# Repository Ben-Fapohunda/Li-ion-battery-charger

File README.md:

# USB-C Smart Li-ion Charger with Live Battery Monitor

A compact single-cell Li-ion/LiPo charger powered over USB-C, with a built-in monitor that shows battery voltage and charge current on a small OLED. The project is designed end to end in KiCad, covering component selection, schematic capture, and PCB layout, and serves as a reference design for small portable power systems.

## Overview

Most low-cost chargers charge a battery and reveal nothing about what is happening. This design adds visibility: voltage and current are measured and displayed in real time while charging, and the power-path architecture lets the board supply a load at the same time.

## Features

- USB-C power input
- Single-cell Li-ion/LiPo charging using the MCP73871 charge management IC, with power-path control
- Voltage and current sensing using an INA219 and a shunt resistor over I2C
- ATtiny1614 microcontroller that reads the sensor and drives a 0.91" I2C OLED
- CH340C USB-to-UART bridge for programming and serial debugging
- AMS1117-3.3 regulator for the logic supply

## Design Approach

The board is split into three functional blocks: power and charging, measurement, and control and display.

Component values were selected around the following:

- **Charge current:** 1 A, set by R_PROG1 = 1 kΩ on the MCP73871 (I = 1000 / R_PROG1 in kΩ)
- **Current sensing:** shunt resistance matched to the INA219 input range
- **Logic supply:** 3.3 V rail from the AMS1117-3.3

The layout is a compact 2-layer board, with attention to current-carrying traces and the placement of the sense resistor.

## Tools

- KiCad for schematic and PCB design
- Arduino/megaTinyCore for ATtiny1614 firmware

## Repository Contents

- `battery charger/`: KiCad project files (schematic and PCB)
- `pcb.png`: PCB layout screenshot
- `pcb view.png`: PCB view screenshot
- `README.md`: project description

## Status

Schematic and PCB layout complete. Not yet fabricated or tested. Photos and measured results will be added after the board is built and tested.

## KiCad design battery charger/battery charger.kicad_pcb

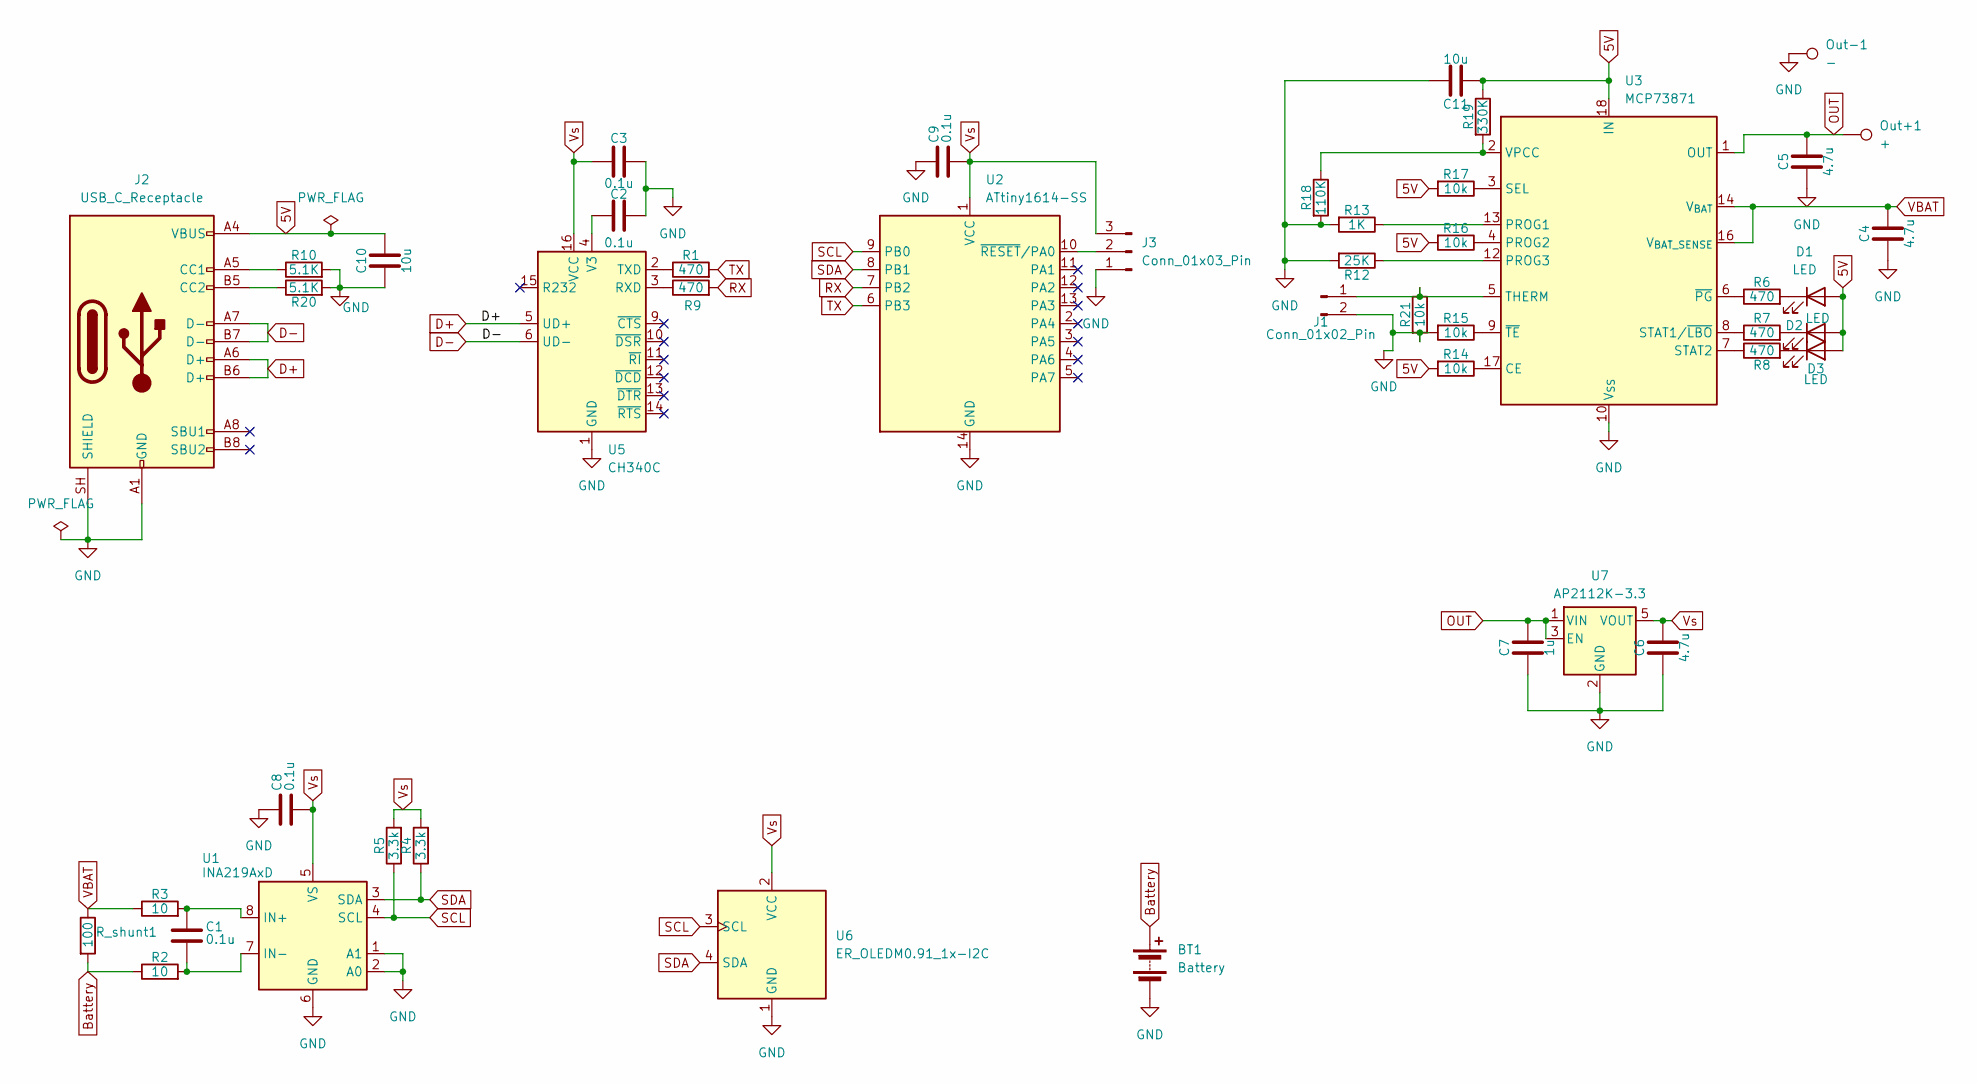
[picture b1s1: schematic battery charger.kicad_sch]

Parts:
BT1: Battery; BatteryHolder_Keystone_2460_1xAA
C1, C2, C3, C8, C9: 0.1u; C_0805_2012Metric
C4, C5, C6: 4.7u; C_0805_2012Metric
C7: 1u; C_0805_2012Metric
C10, C11: 10u; C_0805_2012Metric
D1, D2, D3: LED; LED_0805_2012Metric
J1: Conn_01x02_Pin; PinSocket_1x02_P1.27mm_Vertical
J2: USB_C_Receptacle; USB_C_Receptacle_HRO_TYPE-C-31-M-12
J3: Conn_01x03_Pin; PinSocket_1x03_P1.27mm_Vertical
Out+1: +; SolderWire-0.127sqmm_1x01_D0.48mm_OD1mm
Out-1: -; SolderWire-0.127sqmm_1x01_D0.48mm_OD1mm
R1, R6, R7, R8, R9: 470; R_0805_2012Metric
R2, R3: 10; R_0805_2012Metric
R4, R5: 3.3k; R_0805_2012Metric
R10, R20: 5.1K; R_0805_2012Metric
R12: 25K; R_0805_2012Metric
R13: 1K; R_0805_2012Metric
R14, R15, R16, R17, R21: 10k; R_0805_2012Metric
R18: 110K; R_0805_2012Metric
R19: 330K; R_0805_2012Metric
R_shunt1: 100; R_2512_6332Metric_Pad1.40x3.35mm_HandSolder
U1: INA219AxD; SOIC-8_3.9x4.9mm_P1.27mm
U2: ATtiny1614-SS; SOIC-14_3.9x8.7mm_P1.27mm
U3: MCP73871; QFN-20-1EP_4x4mm_P0.5mm_EP2.5x2.5mm
U5: CH340C; SOIC-16_3.9x9.9mm_P1.27mm
U6: ER_OLEDM0.91_1x-I2C
U7: AP2112K-3.3; SOT-23-5

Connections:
5V: C10.2, C11.1, D1.2 (A), D2.2 (A), D3.2 (A), J2.A4 (VBUS), J2.A9 (VBUS), J2.B4 (VBUS), J2.B9 (VBUS), R14.2, R16.2, R17.2, R19.1, U3.18 (IN), U3.19 (IN)
Battery: BT1.1 (+), R2.1, R_shunt1.2
D+: J2.A6 (D+), J2.B6 (D+), U5.5 (UD+)
D-: J2.A7 (D-), J2.B7 (D-), U5.6 (UD-)
GND: BT1.2 (-), C2.2, C3.2, C4.1, C5.1, C6.1, C7.1, C8.1, C9.1, C10.1, C11.2, J1.2, J2.A1 (GND), J2.A12 (GND), J2.B1 (GND), J2.B12 (GND), J2.SH (SHIELD), J3.1, Out-1.1 (1_1), R10.2, R12.2, R13.2, R15.2, R18.2, R20.2, R21.2, U1.1 (A1), U1.2 (A0), U1.6 (GND), U2.14 (GND), U3.10 (V_{SS}), U3.11 (V_{SS}), U3.21 (V_{SS}), U5.1 (GND), U6.1 (GND), U7.2 (GND)
unnamed: D1.1 (K), R6.2
unnamed: D2.1 (K), R7.2
unnamed: D3.1 (K), R8.2
unnamed: J1.1, R21.1, U3.5 (THERM)
unnamed: J2.A5 (CC1), R10.1
unnamed: J2.B5 (CC2), R20.1
unnamed: J3.2, U2.10 (~RESET/PA0)
unnamed: C1.1, R3.2, U1.8 (IN+)
unnamed: C1.2, R2.2, U1.7 (IN-)
unnamed: R14.1, U3.17 (CE)
unnamed: R13.1, U3.13 (PROG1)
unnamed: R16.1, U3.4 (PROG2)
unnamed: R12.1, U3.12 (PROG3)
unnamed: R17.1, U3.3 (SEL)
unnamed: R7.1, U3.8 (STAT1/~LBO)
unnamed: R8.1, U3.7 (STAT2)
unnamed: R18.1, R19.2, U3.2 (VPCC)
unnamed: R6.1, U3.6 (~PG)
unnamed: R15.1, U3.9 (~TE)
unnamed: R9.1, U5.3 (RXD)
unnamed: R1.1, U5.2 (TXD)
unnamed: C2.1, U5.4 (V3)
OUT: C5.2, C7.2, Out+1.1 (1_1), U3.1 (OUT), U3.20 (OUT), U7.1 (VIN), U7.3 (EN)
RX: R9.2, U2.7 (PB2)
SCL: R5.1, U1.4 (SCL), U2.9 (PB0), U6.3 (SCL)
SDA: R4.1, U1.3 (SDA), U2.8 (PB1), U6.4 (SDA)
TX: R1.2, U2.6 (PB3)
VBAT: C4.2, R3.1, R_shunt1.1, U3.14 (V_{BAT}), U3.15 (V_{BAT}), U3.16 (V_{BAT_SENSE})
Vs: C3.1, C6.2, C8.2, C9.2, J3.3, R4.2, R5.2, U1.5 (VS), U2.1 (VCC), U5.16 (VCC), U6.2 (VCC), U7.5 (VOUT)

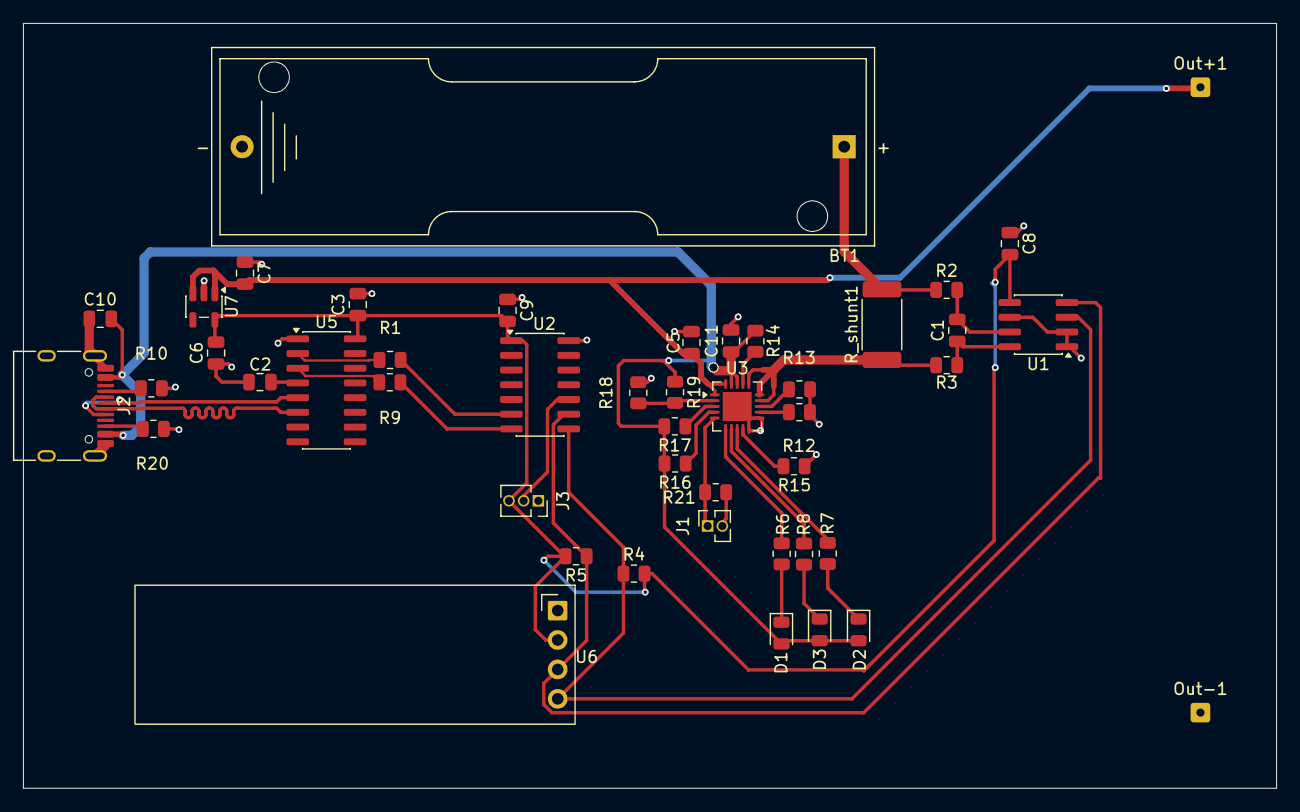
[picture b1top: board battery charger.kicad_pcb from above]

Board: 2 copper layers, 108.2 x 66.0 mm, 46 parts (0 on the bottom side), 34 nets.
